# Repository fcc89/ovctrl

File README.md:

# ROVEN
Testboard for a reflow oven controller

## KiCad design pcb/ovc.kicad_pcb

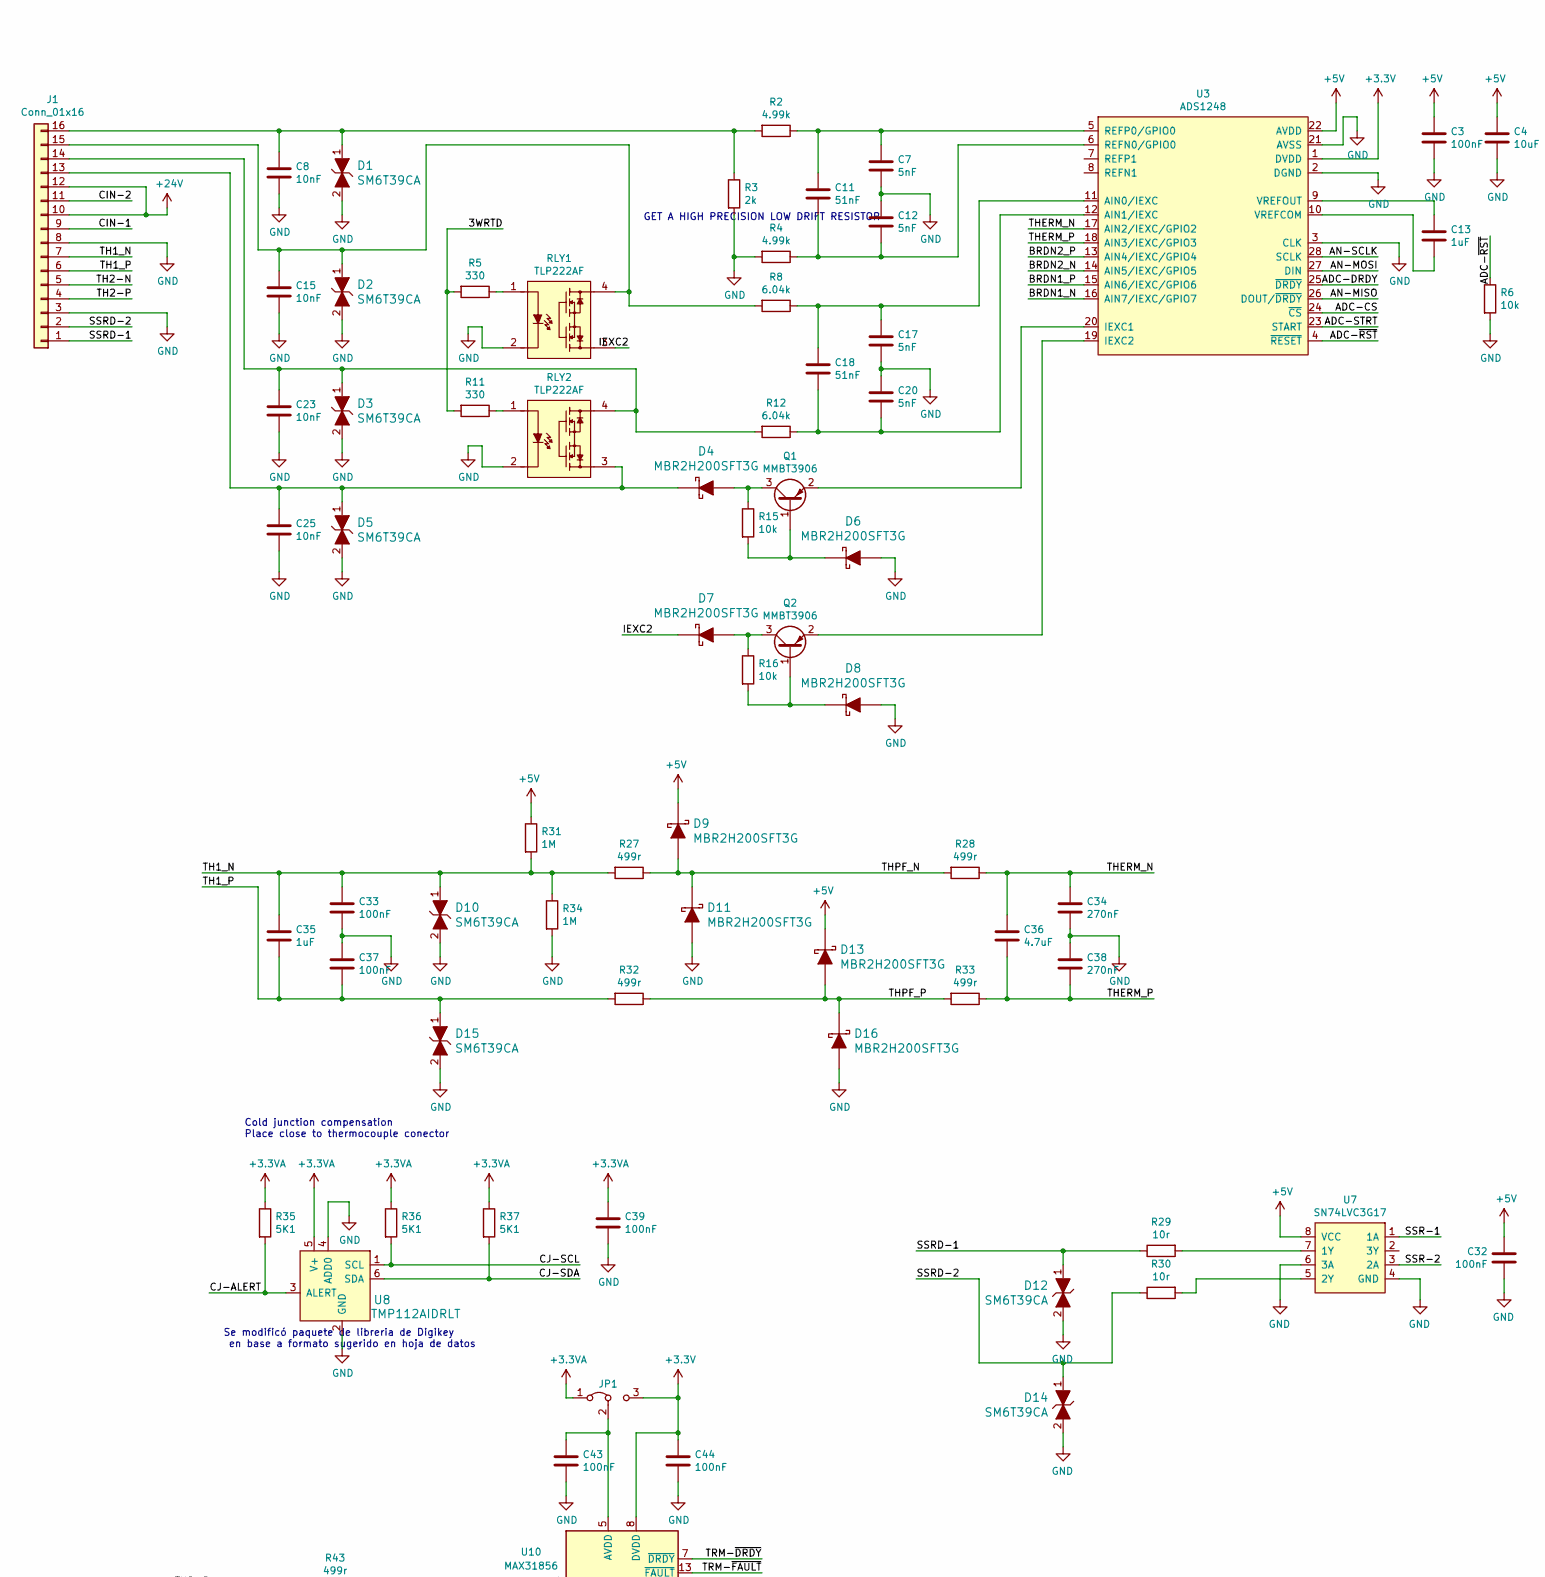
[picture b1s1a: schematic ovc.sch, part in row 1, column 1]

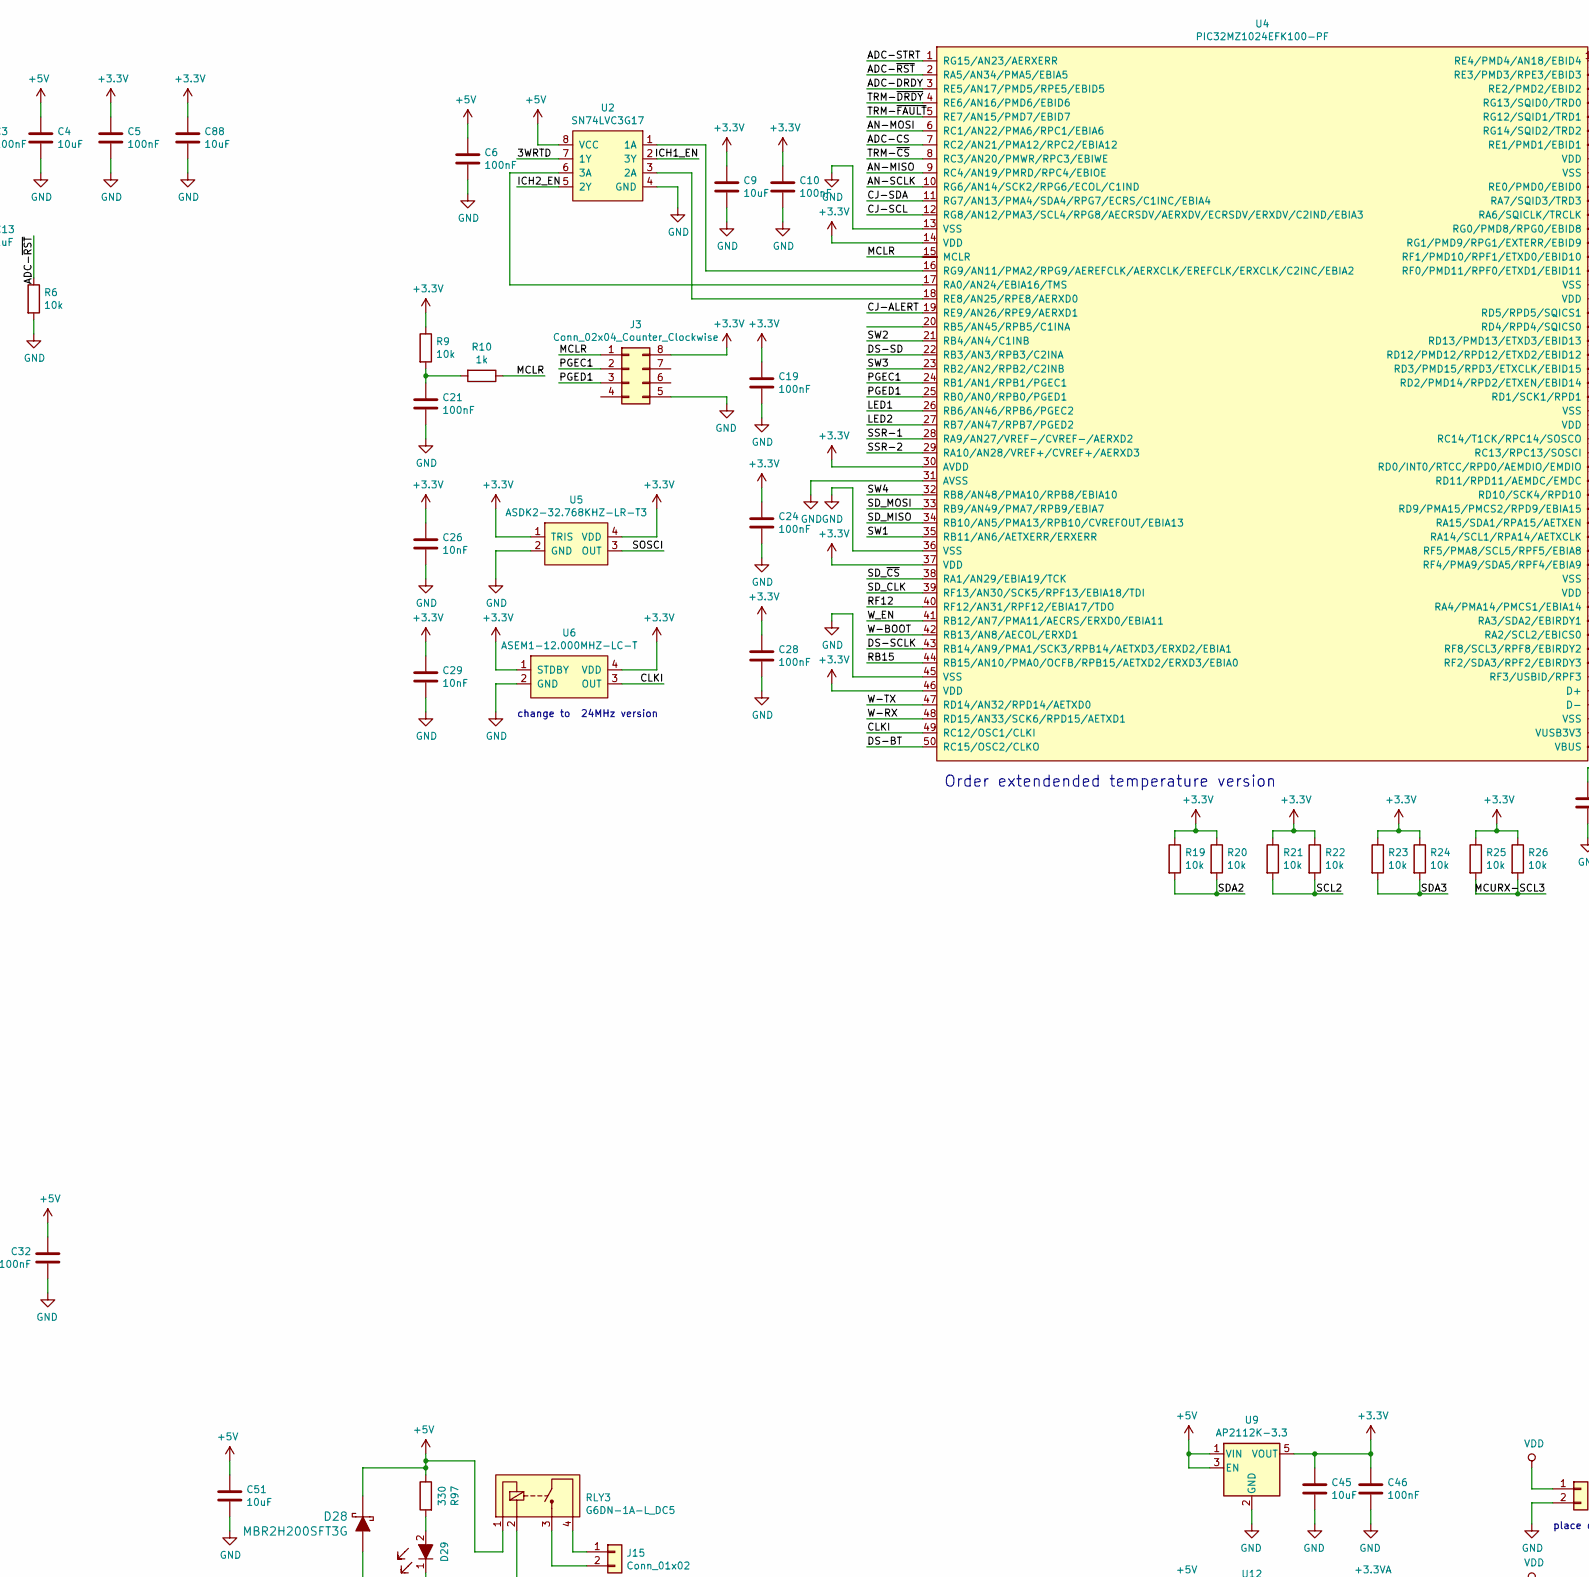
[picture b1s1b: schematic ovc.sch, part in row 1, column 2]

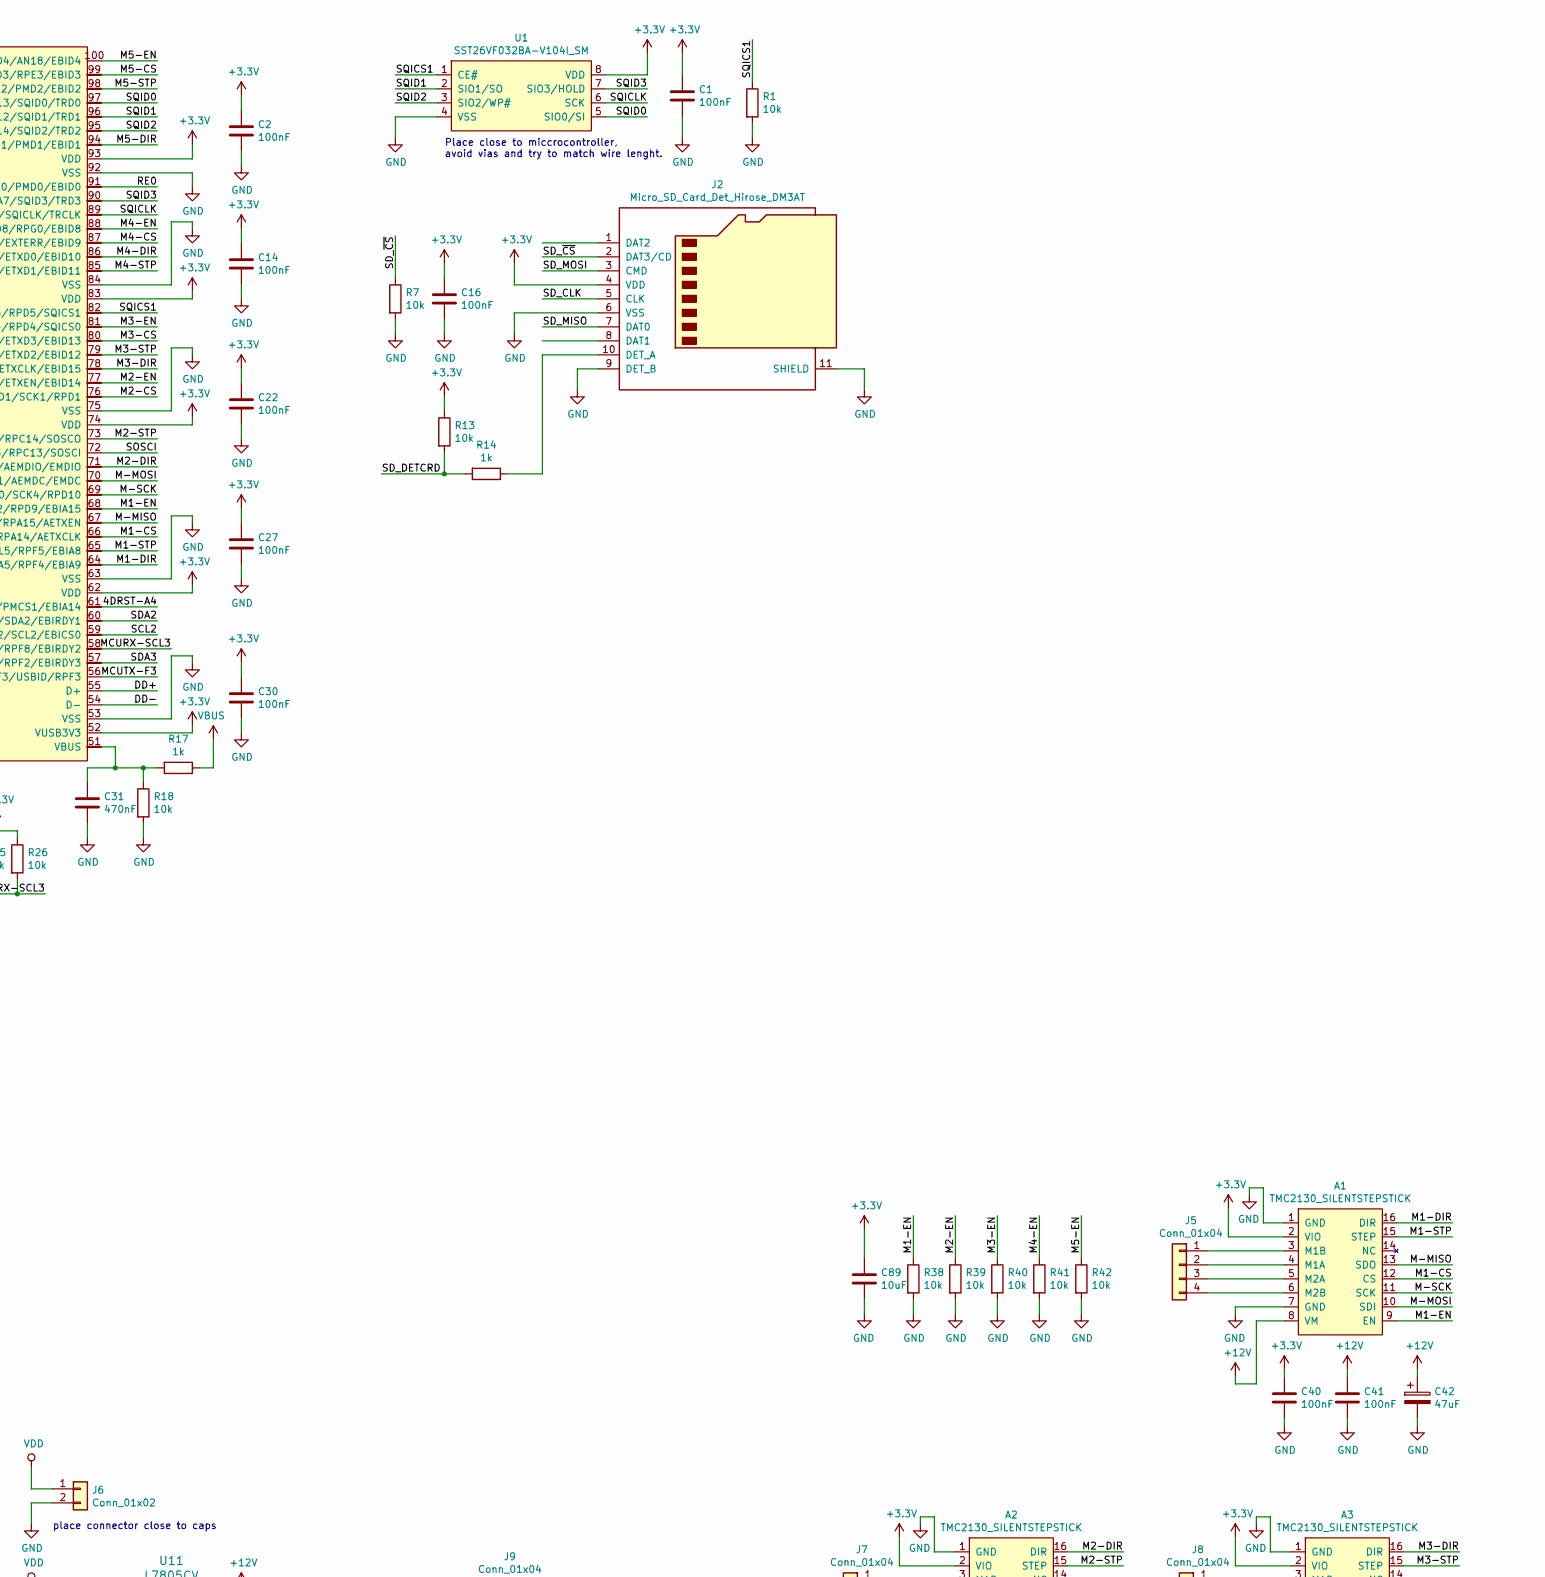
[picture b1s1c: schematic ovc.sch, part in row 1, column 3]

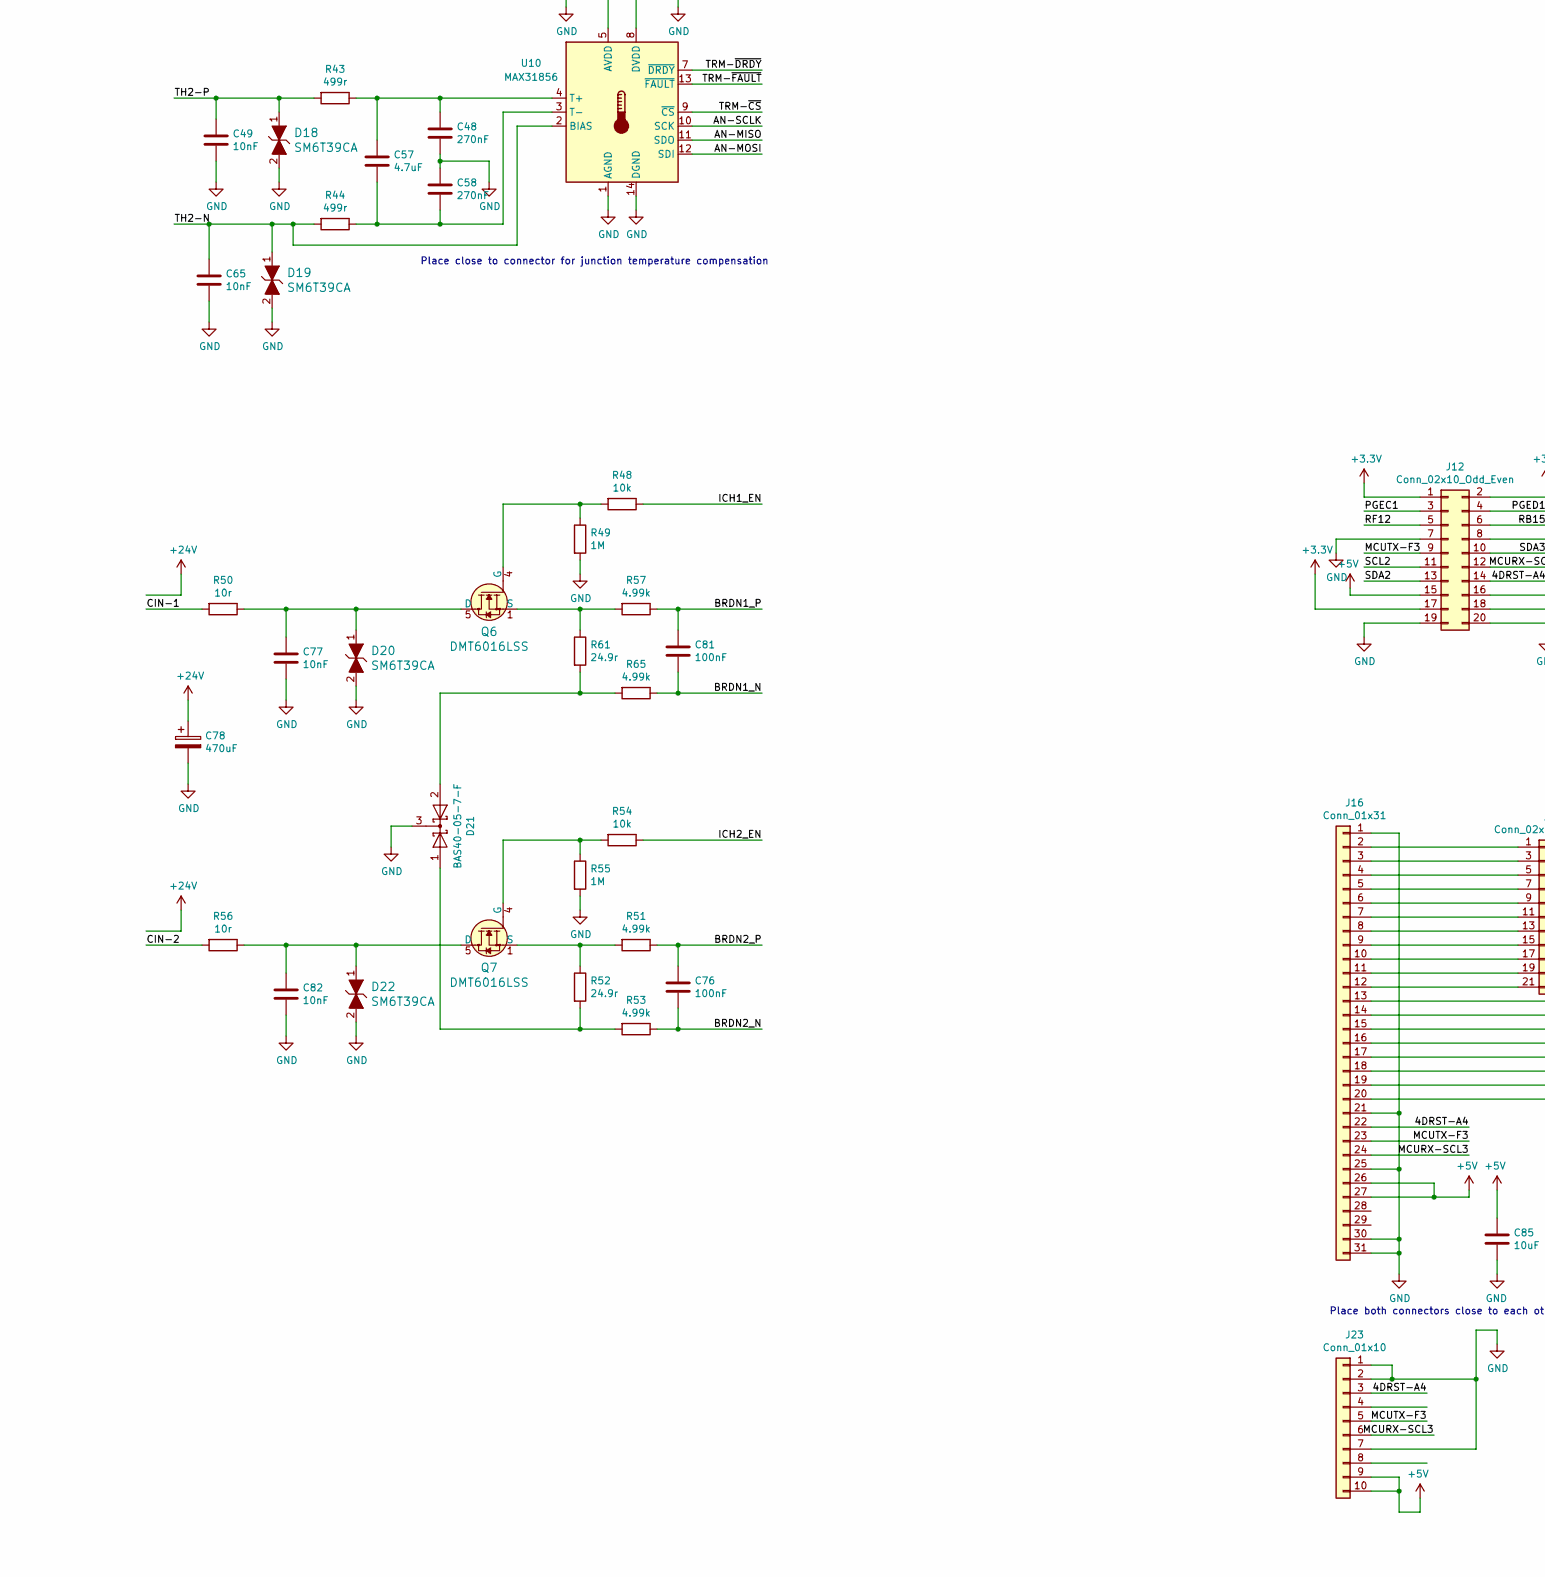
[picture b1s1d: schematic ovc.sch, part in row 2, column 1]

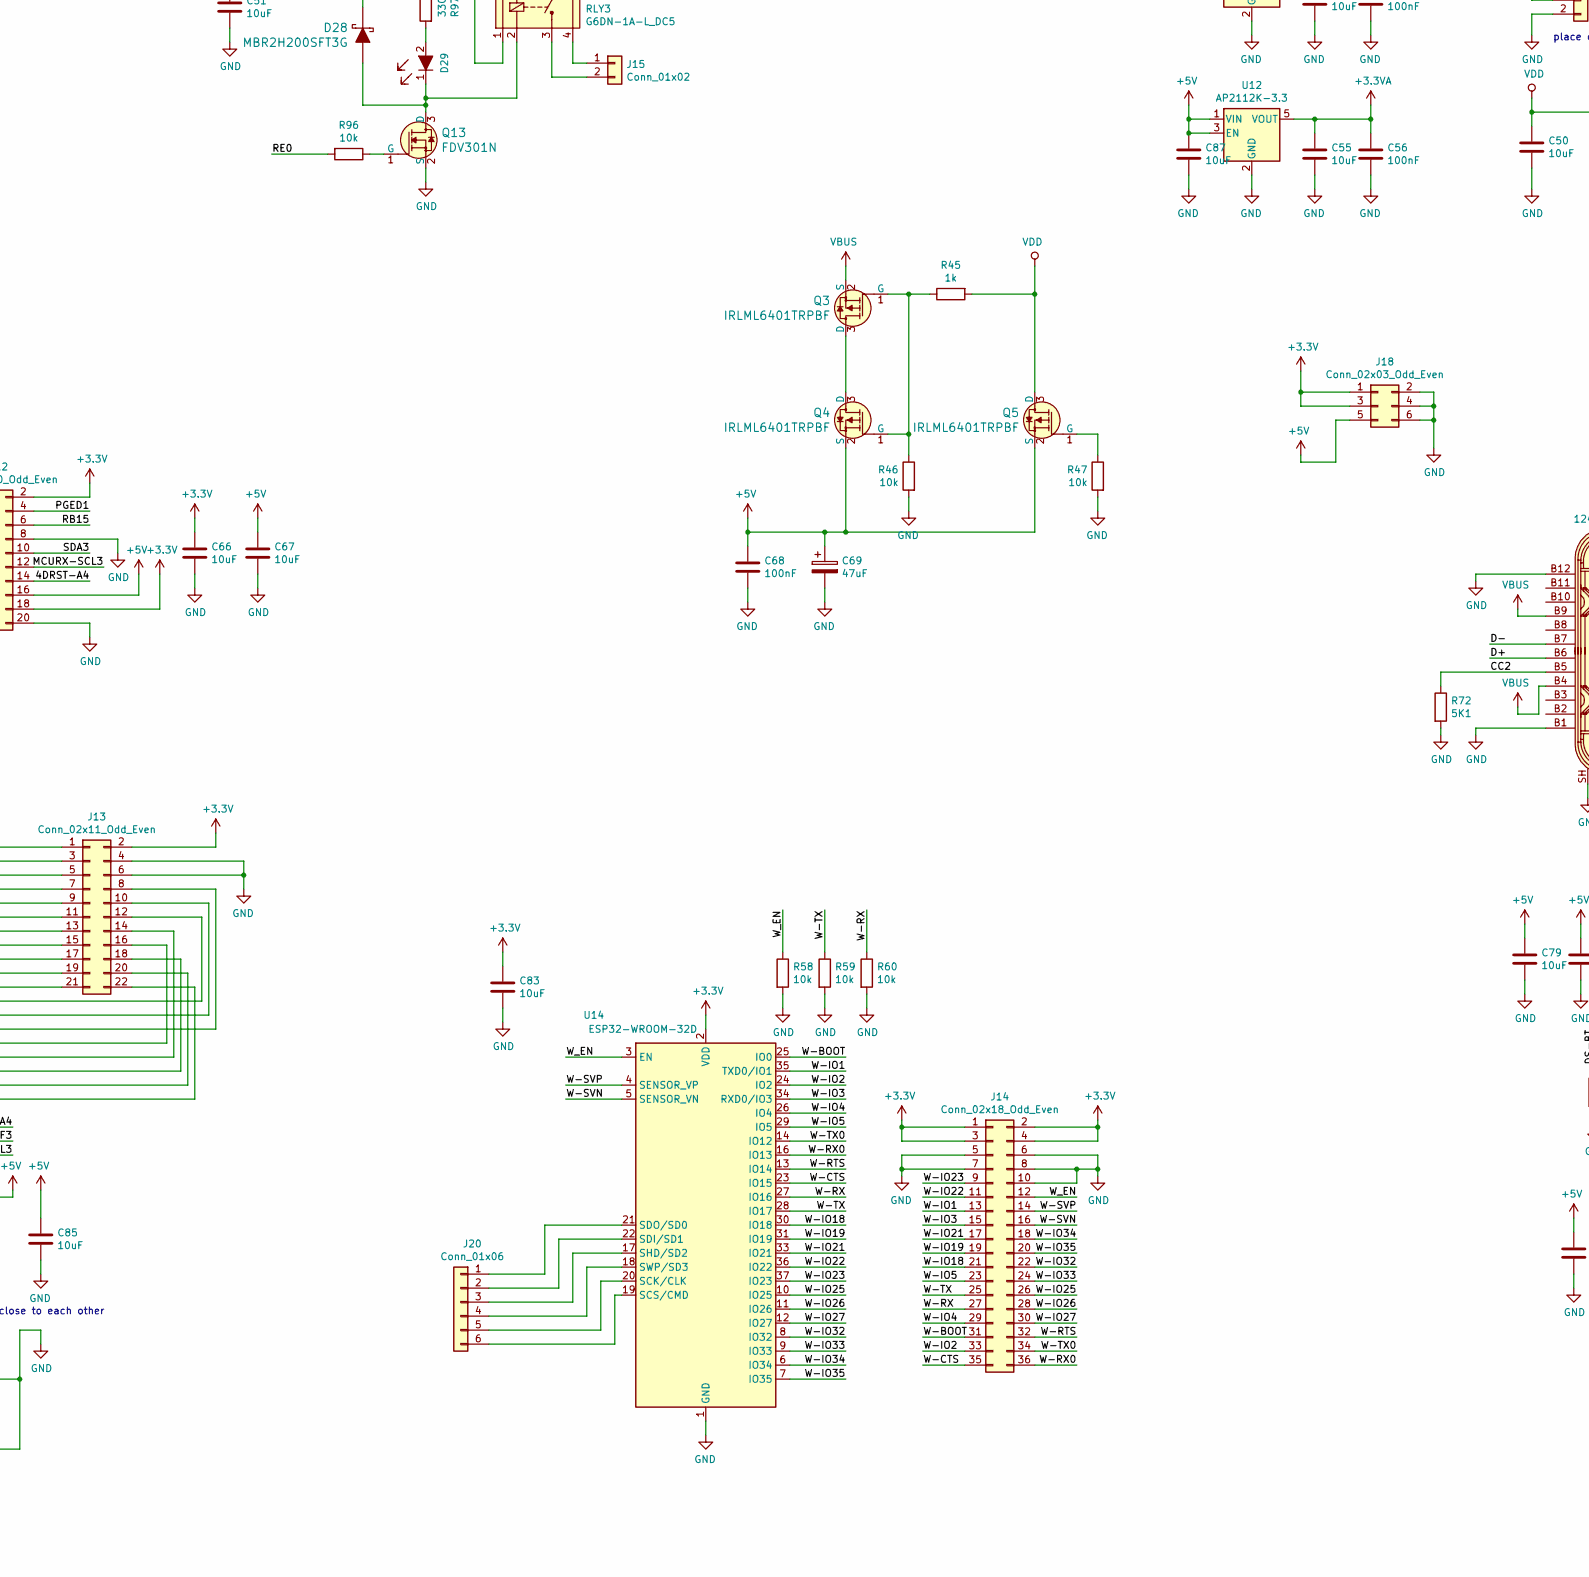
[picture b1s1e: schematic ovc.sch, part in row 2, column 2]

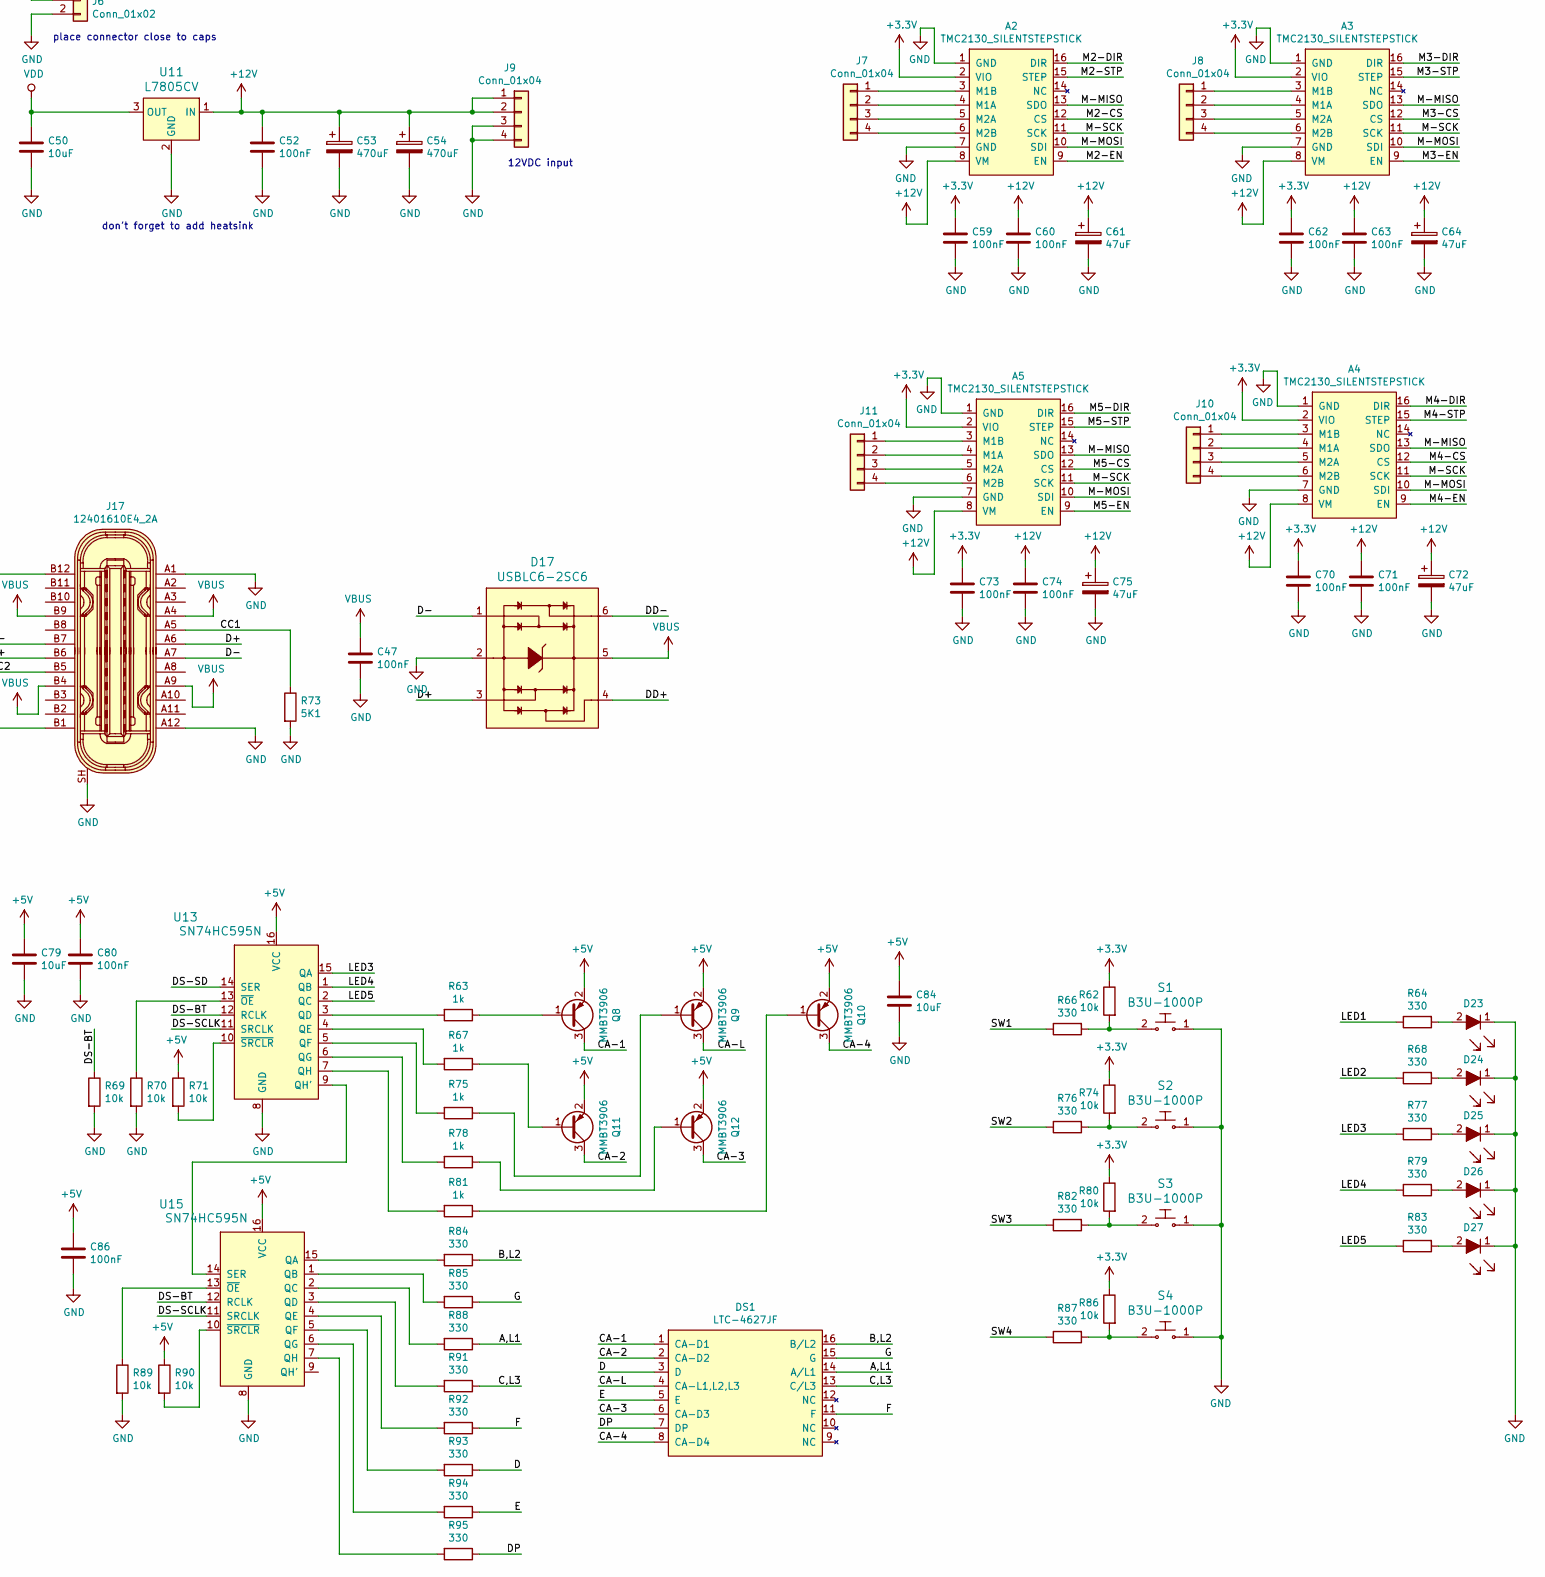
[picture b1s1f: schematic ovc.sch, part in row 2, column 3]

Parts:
A1, A2, A3, A4, A5: TMC2130_SILENTSTEPSTICK; trinamic SILENTSTEPSTICK
C1, C2, C3, C5, C6, C10, C14, C16, C19, C21, C22, C24, C27, C28, C30, C32, C33, C37, C39, C40, C41, C43, C44, C46, C47, C52, C56, C59, C60, C62, C63, C68, C70, C71, C73, C74, C76, C80, C81, C86: 100nF; murata-CAP-GCM-0603-1608metric-reflow
C4, C9, C45, C50, C51, C55, C66, C67, C79, C83, C84, C85, C87, C88, C89: 10uF; murata-CAP-GRM-0805-2012metric-reflow
C7, C12, C17, C20: 5nF; murata-CAP-GCM-0603-1608metric-reflow
C8, C15, C23, C25, C26, C29, C49, C65, C77, C82: 10nF; murata-CAP-GCM-0603-1608metric-reflow
C11, C18: 51nF; murata-CAP-GCM-0603-1608metric-reflow
C13, C35: 1uF; murata-CAP-GRM-0805-2012metric-reflow
C31: 470nF; murata-CAP-GCM-0603-1608metric-reflow
C34, C38, C48, C58: 270nF; murata-CAP-GCM-0603-1608metric-reflow
C36, C57: 4.7uF; murata-CAP-GRM-0805-2012metric-reflow
C42, C61, C64, C69, C72, C75: 47uF; C_Elec_6.3x5.8
C53, C54, C78: 470uF; C_Elec_10x10.2
D1, D2, D3, D5, D10, D12, D14, D15, D18, D19, D20, D22: SM6T39CA; ST-DO214AA; MPN SM6T39CA; Digi-Key_PN 497-6498-1-ND
D4, D6, D7, D8, D9, D11, D13, D16, D28: MBR2H200SFT3G; onsemi-sod123fl; MPN MBR2H200SFT3G; Digi-Key_PN MBR2H200SFT3GOSCT-ND
D17: USBLC6-2SC6; SOT23-6L; MPN USBLC6-2SC6; Digi-Key_PN 497-5235-1-ND
D21: BAS40-05-7-F; SOT-23-3
D23, D24, D25, D26, D27, D29: LTST-C191KRKT; LED_0603; MPN LTST-C191KRKT; Digi-Key_PN 160-1447-1-ND
DS1: LTC-4627JF; liteon-C4627JF
J1: Conn_01x16; phoenix_contact-therminal_block-16pos_PTSA1.5_16-3.5-F-1985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
J2: Micro_SD_Card_Det_Hirose_DM3AT; microSD_HC_Hirose_DM3AT-SF-PEJM5
J3: Conn_02x04_Counter_Clockwise; VC-SOICbite-vcpinout
J5, J7, J8, J10, J11: Conn_01x04; Molex_Nano-Fit_105309-xx04_1x04_P2.50mm_Vertical
J6: Conn_01x02; PinHeader_1x02_P2.54mm_Vertical
J9: Conn_01x04; phoenix_contact-therminal_block-4pos_PTSA1.5-4-3.5-F-1984989
J12: Conn_02x10_Odd_Even; PinHeader_2x10_P2.54mm_Vertical_SMD
J13: Conn_02x11_Odd_Even; PinHeader_2x12_P2.54mm_Vertical_SMD
J14: Conn_02x18_Odd_Even; PinHeader_2x18_P2.54mm_Vertical_SMD
J15: Conn_01x02; phoenix_contact-therminal_block-2pos_PTSA1.5-2-3.5-F-1984963
J16: Conn_01x31; Omron-XF2M-3015-1A
J17: 12401610E4_2A; USB-C_Female_12401X; MPN 12401610E4#2A; Digi-Key_PN 12401610E4#2ACT-ND
J18: Conn_02x03_Odd_Even; PinHeader_2x03_P2.54mm_Vertical
J20: Conn_01x06; PinHeader_1x06_P1.27mm_Vertical_SMD_Pin1Right
J23: Conn_01x10; Hirose_FH12-10S-0.5SH_1x10-1MP_P0.50mm_Horizontal
JP1: Jumper_3_Bridged12; PinHeader_1x03_P2.00mm_Vertical
Q1, Q2, Q8, Q9, Q10, Q11, Q12: MMBT3906; SOT-23
Q3, Q4, Q5: IRLML6401TRPBF; SOT-23-3; MPN IRLML6401TRPBF; Digi-Key_PN IRLML6401PBFCT-ND
Q6, Q7: DMT6016LSS; DIODES-SO8-DMT6016
Q13: FDV301N; SOT-23-3; MPN FDV301N; Digi-Key_PN FDV301NCT-ND
R1, R6, R7, R9, R13, R15, R16, R18, R19, R20, R21, R22, R23, R24, R25, R26, R38, R39, R40, R41, R42, R46, R47, R48, R54, R58, R59, R60, R62, R69, R70, R71, R74, R80, R86, R89, R90, R96: 10k; VC-RES-0603-1608metric
R2, R4, R51, R53, R57, R65: 4.99k; VC-RES-0603-1608metric
R3: 2k; VC-RES-0603-1608metric
R5, R11, R64, R66, R68, R76, R77, R79, R82, R83, R84, R85, R87, R88, R91, R92, R93, R94, R95, R97: 330; VC-RES-0603-1608metric
R8, R12: 6.04k; VC-RES-0603-1608metric
R10, R14, R17, R45, R63, R67, R75, R78, R81: 1k; VC-RES-0603-1608metric
R27, R28, R32, R33, R43, R44: 499r; VC-RES-0603-1608metric
R29, R30, R50, R56: 10r; VC-RES-0603-1608metric
R31, R34, R49, R55: 1M; VC-RES-0603-1608metric
R35, R36, R37, R72, R73: 5K1; VC-RES-0603-1608metric
R52, R61: 24.9r; 1206
RLY1, RLY2: TLP222AF; DIP-4_W7.62mm; MPN TLP222AF; Digi-Key_PN TLP222AF-ND
RLY3: G6DN-1A-L_DC5; Omron G6DN-1A
S1, S2, S3, S4: B3U-1000P; Switch_Tactile_SMD_B3U-1000P; MPN B3U-1000P; Digi-Key_PN SW1020CT-ND
U1: SST26VF032BA-V104I_SM; Microchip-SOIJ-8-1.27mm
U2, U7: SN74LVC3G17; TexasInstruments_DCU8_R-PDSO-G8_0.5mm
U3: ADS1248; texasInstruments-sop-28-PW_R-PDSO-G28
U4: PIC32MZ1024EFK100-PF; Microchip-TQFP-100_14x14_Pitch0.5mm
U5: ASDK2-32.768KHZ-LR-T3; Abracon-ASDK-2.5x2mm_hand-solder
U6: ASEM1-12.000MHZ-LC-T; Abracon-ASEM-3.2x2.5mm_hand-solder
U8: TMP112AIDRLT; SOT-563; MPN TMP112AIDRLT; Digi-Key_PN 296-24621-1-ND
U9, U12: AP2112K-3.3; SOT-23-5
U10: MAX31856; TSSOP-14_4.4x5mm_P0.65mm
U11: L7805CV; TO-220-3; MPN L7805CV; Digi-Key_PN 497-1443-5-ND
U13, U15: SN74HC595N; SOIC-16_W3.90mm; MPN SN74HC595N; Digi-Key_PN 296-1600-5-ND
U14: ESP32-WROOM-32D; ESP32-WROOM-32

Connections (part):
+3.3VA: C39.1, C55.1, C56.1, JP1.1 (A), R35.1, R36.1, R37.1, U8.5 (V+), U12.5 (VOUT)
+3V3: A1.2 (VIO), A2.2 (VIO), A3.2 (VIO), A4.2 (VIO), A5.2 (VIO), C1.1, C2.1, C5.1, C9.1, C10.1, C14.1, C16.1, C19.1, C22.1, C24.1, C26.1, C27.1, C28.1, C29.1, C30.1, C40.1, C44.1, C45.1, C46.1, C59.1, C62.1, C66.1, C70.1, C73.1, C83.1, C88.1, C89.1, J2.4 (VDD), J3.8, J12.1, J12.2, J12.17, J12.18, J13.2, J14.1, J14.2, J14.3, J14.4, J18.1, J18.3, JP1.3 (B), R9.1, R13.1, R19.1, R20.1, R21.1, R22.1, R23.1, R24.1, R25.1, R26.1, R62.1, R74.1, R80.1, R86.1, U1.8 (VDD), U3.1 (DVDD), U4.14 (VDD), U4.30 (AVDD), U4.37 (VDD), U4.46 (VDD), U4.52 (VUSB3V3), U4.62 (VDD), U4.74 (VDD), U4.83 (VDD), U4.93 (VDD), U5.1 (TRIS), U5.4 (VDD), U6.1 (STDBY), U6.4 (VDD), U9.5 (VOUT), U10.8 (DVDD), U14.2 (VDD)
+5V: C3.1, C4.1, C6.1, C32.1, C51.1, C67.1, C68.1, C69.1, C79.1, C80.1, C84.1, C85.1, C86.1, C87.1, D9.K, D13.K, D28.K, J12.15, J12.16, J16.26, J16.27, J18.5, J23.9, J23.10, Q4.2 (S), Q5.2 (S), Q8.2 (E), Q9.2 (E), Q10.2 (E), Q11.2 (E), Q12.2 (E), R31.1, R71.1, R90.1, R97.1, RLY3.1 (C1), U2.8 (VCC), U3.22 (AVDD), U7.8 (VCC), U9.1 (VIN), U9.3 (EN), U12.1 (VIN), U12.3 (EN), U13.16 (VCC), U15.16 (VCC)
+12V: A1.8 (VM), A2.8 (VM), A3.8 (VM), A4.8 (VM), A5.8 (VM), C41.1, C42.1, C52.1, C53.1, C54.1, C60.1, C61.1, C63.1, C64.1, C71.1, C72.1, C74.1, C75.1, J9.1, J9.2, U11.1 (IN)
+24V: C78.1, J1.10, J1.12
/3WRTD: R5.2, R11.2, U2.7 (1Y)
/4DRST-A4: J12.14, J16.22, J23.3, U4.61 (RA4/PMA14/PMCS1/EBIA14)
/A,L1: DS1.14 (A/L1), R88.1
/ADC-CS: U3.24 (~CS~), U4.7 (RC2/AN21/PMA12/RPC2/EBIA12)
/ADC-DRDY: U3.25 (~DRDY~), U4.3 (RE5/AN17/PMD5/RPE5/EBID5)
/ADC-STRT: U3.23 (START), U4.1 (RG15/AN23/AERXERR)
/ADC-~RST~: R6.1, U3.4 (~RESET~), U4.2 (RA5/AN34/PMA5/EBIA5)
/AN-MISO: U3.26 (DOUT/~DRDY~), U4.9 (RC4/AN19/PMRD/RPC4/EBIOE), U10.11 (SDO)
/AN-MOSI: U3.27 (DIN), U4.6 (RC1/AN22/PMA6/RPC1/EBIA6), U10.12 (SDI)
/AN-SCLK: U3.28 (SCLK), U4.10 (RG6/AN14/SCK2/RPG6/ECOL/C1IND), U10.10 (SCK)
/B,L2: DS1.16 (B/L2), R84.1
/BRDN1_N: C81.2, R65.1, U3.16 (AIN7/IEXC/GPIO7)
/BRDN1_P: C81.1, R57.1, U3.15 (AIN6/IEXC/GPIO6)
/BRDN2_N: C76.2, R53.1, U3.14 (AIN5/IEXC/GPIO5)
/BRDN2_P: C76.1, R51.1, U3.13 (AIN4/IEXC/GPIO4)
/C,L3: DS1.13 (C/L3), R91.1
/CA-1: DS1.1 (CA-D1), Q8.3 (C)
/CA-2: DS1.2 (CA-D2), Q11.3 (C)
/CA-3: DS1.6 (CA-D3), Q12.3 (C)
/CA-4: DS1.8 (CA-D4), Q10.3 (C)
/CA-L: DS1.4 (CA-L1,L2,L3), Q9.3 (C)
/CC1: J17.A5, R73.1
/CC2: J17.B5, R72.1
/CIN-1: J1.9, R50.2
/CIN-2: J1.11, R56.2
/CJ-ALERT: R35.2, U4.19 (RE9/AN26/RPE9/AERXD1), U8.3 (ALERT)
/CJ-SCL: R36.2, U4.12 (RG8/AN12/PMA3/SCL4/RPG8/AECRSDV/AERXDV/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), U8.1 (SCL)
/CJ-SDA: R37.2, U4.11 (RG7/AN13/PMA4/SDA4/RPG7/ECRS/C1INC/EBIA4), U8.6 (SDA)
/CLKI: U4.49 (RC12/OSC1/CLKI), U6.3 (OUT)
/D: DS1.3 (D), R93.1
/D+: D17.3, J17.A6, J17.B6
/D-: D17.1, J17.A7, J17.B7
/DD+: D17.4, U4.55 (D+)
/DD-: D17.6, U4.54 (D-)
/DP: DS1.7 (DP), R95.1
/DS-BT: R69.1, U4.50 (RC15/OSC2/CLKO), U13.12 (RCLK), U15.12 (RCLK)
/DS-SCLK: U4.43 (RB14/AN9/PMA1/SCK3/RPB14/AETXD3/ERXD2/E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), U13.11 (SRCLK), U15.11 (SRCLK)
/DS-SD: U4.22 (RB3/AN3/RPB3/C2INA), U13.14 (SER)
/E: DS1.5 (E), R94.1
/F: DS1.11 (F), R92.1
/G: DS1.15 (G), R85.1
/ICH1_EN: R48.1, U2.2 (3Y)
/ICH2_EN: R54.1, U2.5 (2Y)
/IEXC2: D7.K, RLY1.3 (DRAIN)
/LED1: R64.1, U4.26 (RB6/AN46/RPB6/PGEC2)
/LED2: R68.1, U4.27 (RB7/AN47/RPB7/PGED2)
/LED3: R77.1, U13.15 (QA)
/LED4: R79.1, U13.1 (QB)
/LED5: R83.1, U13.2 (QC)
/M1-CS: A1.12 (CS), U4.66 (RA14/SCL1/RPA14/AETXCLK)
/M1-DIR: A1.16 (DIR), U4.64 (RF4/PMA9/SDA5/RPF4/EBIA9)
/M1-EN: A1.9 (EN), R38.1, U4.68 (RD9/PMA15/PMCS2/RPD9/EBIA15)
/M1-STP: A1.15 (STEP), U4.65 (RF5/PMA8/SCL5/RPF5/EBIA8)
/M2-CS: A2.12 (CS), U4.76 (RD1/SCK1/RPD1)
/M2-DIR: A2.16 (DIR), U4.71 (RD0/INT0/RTCC/RPD0/AEMDIO/EMDIO)
/M2-EN: A2.9 (EN), R39.1, U4.77 (RD2/PMD14/RPD2/ETXEN/EBID14)
/M2-STP: A2.15 (STEP), U4.73 (RC14/T1CK/RPC14/SOSCO)
/M3-CS: A3.12 (CS), U4.80 (RD13/PMD13/ETXD3/EBID13)
/M3-DIR: A3.16 (DIR), U4.78 (RD3/PMD15/RPD3/ETXCLK/EBID15)
/M3-EN: A3.9 (EN), R40.1, U4.81 (RD4/RPD4/SQICS0)
/M3-STP: A3.15 (STEP), U4.79 (RD12/PMD12/RPD12/ETXD2/EBID12)
/M4-CS: A4.12 (CS), U4.87 (RG1/PMD9/RPG1/EXTERR/EBID9)
/M4-DIR: A4.16 (DIR), U4.86 (RF1/PMD10/RPF1/ETXD0/EBID10)
/M4-EN: A4.9 (EN), R41.1, U4.88 (RG0/PMD8/RPG0/EBID8)
/M4-STP: A4.15 (STEP), U4.85 (RF0/PMD11/RPF0/ETXD1/EBID11)
/M5-CS: A5.12 (CS), U4.99 (RE3/PMD3/RPE3/EBID3)
/M5-DIR: A5.16 (DIR), U4.94 (RE1/PMD1/EBID1)
/M5-EN: A5.9 (EN), R42.1, U4.100 (RE4/PMD4/AN18/EBID4)
/M5-STP: A5.15 (STEP), U4.98 (RE2/PMD2/EBID2)
/M-MISO: A1.13 (SDO), A2.13 (SDO), A3.13 (SDO), A4.13 (SDO), A5.13 (SDO), U4.67 (RA15/SDA1/RPA15/AETXEN)
/M-MOSI: A1.10 (SDI), A2.10 (SDI), A3.10 (SDI), A4.10 (SDI), A5.10 (SDI), U4.70 (RD11/RPD11/AEMDC/EMDC)
/M-SCK: A1.11 (SCK), A2.11 (SCK), A3.11 (SCK), A4.11 (SCK), A5.11 (SCK), U4.69 (RD10/SCK4/RPD10)
/MCLR: J3.1, R10.1, U4.15 (MCLR)
/MCURX-SCL3: J12.12, J16.24, J23.6, R25.2, R26.2, U4.58 (RF8/SCL3/RPF8/EBIRDY2)
/MCUTX-F3: J12.9, J16.23, J23.5, U4.56 (RF3/USBID/RPF3)
/PGEC1: J3.2, J12.3, U4.24 (RB1/AN1/RPB1/PGEC1)
/PGED1: J3.3, J12.4, U4.25 (RB0/AN0/RPB0/PGED1)
/RB15: J12.6, U4.44 (RB15/AN10/PMA0/OCFB/RPB15/AETXD2/ERXD3/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)
/RE0: R96.2, U4.91 (RE0/PMD0/EBID0)
/RF12: J12.5, U4.40 (RF12/AN31/RPF12/EBIA17/TDO)
/SCL2: J12.11, R21.2, R22.2, U4.59 (RA2/SCL2/EBICS0)
/SDA2: J12.13, R19.2, R20.2, U4.60 (RA3/SDA2/EBIRDY1)
/SDA3: J12.10, R23.2, R24.2, U4.57 (RF2/SDA3/RPF2/EBIRDY3)
/SD_CLK: J2.5 (CLK), U4.39 (RF13/AN30/SCK5/RPF13/EBIA18/TDI)
/SD_DETCRD: R13.2, R14.2
/SD_MISO: J2.7 (DAT0), U4.34 (RB10/AN5/PMA13/RPB10/CVREFOUT/EBIA13)
/SD_MOSI: J2.3 (CMD), U4.33 (RB9/AN49/PMA7/RPB9/EBIA7)
/SD_~CS~: J2.2 (DAT3/CD), R7.1, U4.38 (RA1/AN29/EBIA19/TCK)
/SOSCI: U4.72 (RC13/RPC13/SOSCI), U5.3 (OUT)
/SQICLK: U1.6 (SCK), U4.89 (RA6/SQICLK/TRCLK)
/SQICS1: R1.1, U1.1 (CE#), U4.82 (RD5/RPD5/SQICS1)
/SQID0: U1.5 (SIO0/SI), U4.97 (RG13/SQID0/TRD0)
/SQID1: U1.2 (SIO1/SO), U4.96 (RG12/SQID1/TRD1)
/SQID2: U1.3 (SIO2/WP#), U4.95 (RG14/SQID2/TRD2)
/SQID3: U1.7 (SIO3/HOLD), U4.90 (RA7/SQID3/TRD3)
/SSR-1: U4.28 (RA9/AN27/VREF-/CVREF-/AERXD2), U7.1 (1A)
/SSR-2: U4.29 (RA10/AN28/VREF+/CVREF+/AERXD3), U7.3 (2A)
/SSRD-1: D12.1, J1.1, R29.1
/SSRD-2: D14.1, J1.2, R30.1
/SW1: R66.1, U4.35 (RB11/AN6/AETXERR/ERXERR)
/SW2: R76.1, U4.21 (RB4/AN4/C1INB)
/SW3: R82.1, U4.23 (RB2/AN2/RPB2/C2INB)
/SW4: R87.1, U4.32 (RB8/AN48/PMA10/RPB8/EBIA10)
/TH1_N: C33.1, C35.1, D10.1, J1.7, R27.2, R31.2, R34.1
/TH1_P: C35.2, C37.2, D15.1, J1.6, R32.2
/TH2-N: C65.1, D19.1, J1.5, R44.2, U10.2 (BIAS)
/TH2-P: C49.1, D18.1, J1.4, R43.2
/THERM_N: C34.1, C36.1, R28.1, U3.17 (AIN2/IEXC/GPIO2)
/THERM_P: C36.2, C38.2, R33.1, U3.18 (AIN3/IEXC/GPIO3)
/THPF_N: D9.A, D11.K, R27.1, R28.2
/THPF_P: D13.A, D16.K, R32.1, R33.2
/TRM-~CS~: U4.8 (RC3/AN20/PMWR/RPC3/EBIWE), U10.9 (~CS)
/TRM-~DRDY~: U4.4 (RE6/AN16/PMD6/EBID6), U10.7 (~DRDY)
/TRM-~FAULT~: U4.5 (RE7/AN15/PMD7/EBID7), U10.13 (~FAULT)
/W-BOOT: J14.31, U4.42 (RB13/AN8/AECOL/ERXD1), U14.25 (IO0)
/W-CTS: J14.35, U14.23 (IO15)
/W-IO1: J14.13, U14.35 (TXD0/IO1)
/W-IO2: J14.33, U14.24 (IO2)
/W-IO3: J14.15, U14.34 (RXD0/IO3)
/W-IO4: J14.29, U14.26 (IO4)
/W-IO5: J14.23, U14.29 (IO5)
/W-IO18: J14.21, U14.30 (IO18)
/W-IO19: J14.19, U14.31 (IO19)
/W-IO21: J14.17, U14.33 (IO21)
/W-IO22: J14.11, U14.36 (IO22)
/W-IO23: J14.9, U14.37 (IO23)
/W-IO25: J14.26, U14.10 (IO25)
/W-IO26: J14.28, U14.11 (IO26)
/W-IO27: J14.30, U14.12 (IO27)
/W-IO32: J14.22, U14.8 (IO32)
/W-IO33: J14.24, U14.9 (IO33)
/W-IO34: J14.18, U14.6 (IO34)
/W-IO35: J14.20, U14.7 (IO35)
/W-RTS: J14.32, U14.13 (IO14)
/W-RX: J14.27, R60.1, U4.48 (RD15/AN33/SCK6/RPD15/AETXD1), U14.27 (IO16)
/W-RX0: J14.36, U14.16 (IO13)
/W-SVN: J14.16, U14.5 (SENSOR_VN)
/W-SVP: J14.14, U14.4 (SENSOR_VP)
/W-TX: J14.25, R59.1, U4.47 (RD14/AN32/RPD14/AETXD0), U14.28 (IO17)
/W-TX0: J14.34, U14.14 (IO12)
/W_EN: J14.12, R58.1, U4.41 (RB12/AN7/PMA11/AECRS/ERXD0/EBIA11), U14.3 (EN)
GND: A1.1 (GND), A1.7 (GND), A2.1 (GND), A2.7 (GND), A3.1 (GND), A3.7 (GND), A4.1 (GND), A4.7 (GND), A5.1 (GND), A5.7 (GND), C1.2, C2.2, C3.2, C4.2, C5.2, C6.2, C7.2, C8.2, C9.2, C10.2, C12.1, C14.2, C15.2, C16.2, C17.2, C19.2, C20.1, C21.2, C22.2, C23.2, C24.2, C25.2, C26.2, C27.2, C28.2, C29.2, C30.2, C31.2, C32.2, C33.2, C34.2, C37.1, C38.1, C39.2, C40.2, C41.2, C42.2, C43.2, C44.2, C45.2, C46.2, C47.2, C48.2, C49.2, C50.2, C51.2, C52.2, C53.2, C54.2, C55.2, C56.2, C58.1, C59.2, C60.2, C61.2, C62.2, C63.2, C64.2, C65.2, C66.2, C67.2, C68.2, C69.2, C70.2, C71.2, C72.2, C73.2, C74.2, C75.2, C77.2, C78.2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
unnamed: A1.3 (M1B), J5.1
unnamed: A1.4 (M1A), J5.2
unnamed: A1.5 (M2A), J5.3
unnamed: A1.6 (M2B), J5.4
unnamed: A2.3 (M1B), J7.1
unnamed: A2.4 (M1A), J7.2
unnamed: A2.5 (M2A), J7.3
unnamed: A2.6 (M2B), J7.4
unnamed: A3.3 (M1B), J8.1
unnamed: A3.4 (M1A), J8.2
unnamed: A3.5 (M2A), J8.3
unnamed: A3.6 (M2B), J8.4
unnamed: A4.3 (M1B), J10.1
unnamed: A4.4 (M1A), J10.2
unnamed: A4.5 (M2A), J10.3
unnamed: A4.6 (M2B), J10.4
unnamed: A5.3 (M1B), J11.1
unnamed: A5.4 (M1A), J11.2
unnamed: A5.5 (M2A), J11.3
unnamed: A5.6 (M2B), J11.4
unnamed: C8.1, D1.1, J1.16, R2.2, R3.1
unnamed: C7.1, C11.1, R2.1, U3.5 (REFP0/GPIO0)
unnamed: C11.2, C12.2, R4.1, U3.6 (REFN0/GPIO0)
unnamed: C13.1, U3.9 (VREFOUT)
unnamed: C13.2, U3.10 (VREFCOM)
unnamed: C15.1, D2.1, J1.15, R8.2, RLY1.4 (DRAIN)
unnamed: C17.1, C18.1, R8.1, U3.11 (AIN0/IEXC)
unnamed: C18.2, C20.2, R12.1, U3.12 (AIN1/IEXC)
unnamed: C21.1, R9.2, R10.2
unnamed: C23.1, D3.1, J1.14, R12.2, RLY2.4 (DRAIN)
unnamed: C25.1, D4.K, D5.1, J1.13, RLY2.3 (DRAIN)
unnamed: C31.1, R17.2, R18.1, U4.51 (VBUS)
unnamed: C43.1, JP1.2 (C), U10.5 (AVDD)
unnamed: C48.1, C57.1, R43.1, U10.4 (T+)
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
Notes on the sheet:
Cold junction compensation Place close to thermocouple conector
Order extendended temperature version
place connector close to caps
don't forget to add heatsink
12VDC input
Place close to miccrocontroller, avoid vias and try to match wire lenght.
Place close to connector for junction temperature compensation
Place both connectors close to each other
GET A HIGH PRECISION LOW DRIFT RESISTOR
Se modificó paquete de libreria de Digikey en base a formato sugerido en hoja de datos
change to 24MHz version

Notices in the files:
firmware/boardTest/firmware/src/config/default/peripheral/gpio/plib_gpio.h:
Copyright (C) 2019 Microchip Technology Inc. and its subsidiaries.
